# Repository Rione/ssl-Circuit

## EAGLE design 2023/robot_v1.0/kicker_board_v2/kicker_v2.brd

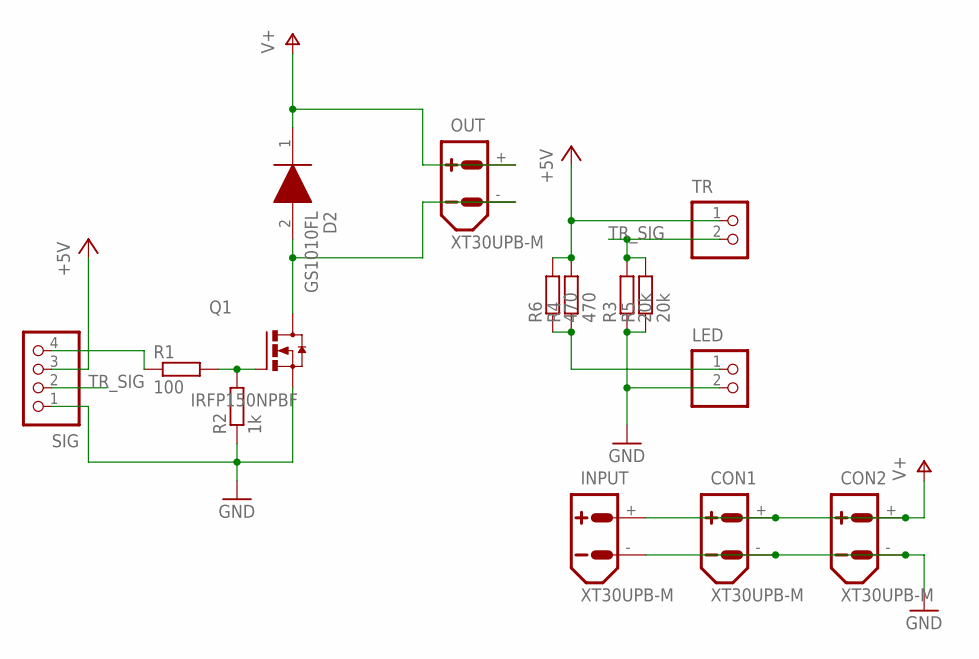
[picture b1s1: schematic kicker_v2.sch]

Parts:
CON1, CON2: XT30UPB-M
D2: GS1010FL; SODFL3618X110N
INPUT: XT30UPB-M
LED: S2B-XH-A
OUT: XT30UPB-M
Q1: IRFP150NPBF; TO-247AC
R1: 100; R0603
R2: 1k; R0603
R3: 20k; 0207/10
R4: 470; 0207/10
R5: 20k; R0603
R6: 470; R0603
SIG: B4B-XH-A
TR: S2B-XH-A

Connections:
1: D2.2 (A), OUT.-, Q1.D
+5V: R4.2, R6.2, SIG.3, TR.1
GND: CON1.-, CON2.-, INPUT.-, LED.2, Q1.S, R2.1, R3.1, R5.1, SIG.1
unnamed: R1.1, SIG.4
unnamed: Q1.G, R1.2, R2.2
unnamed: LED.1, R4.1, R6.1
TR_SIG: R3.2, R5.2, SIG.2, TR.2
V+: CON1.+, CON2.+, D2.1 (K), INPUT.+, OUT.+

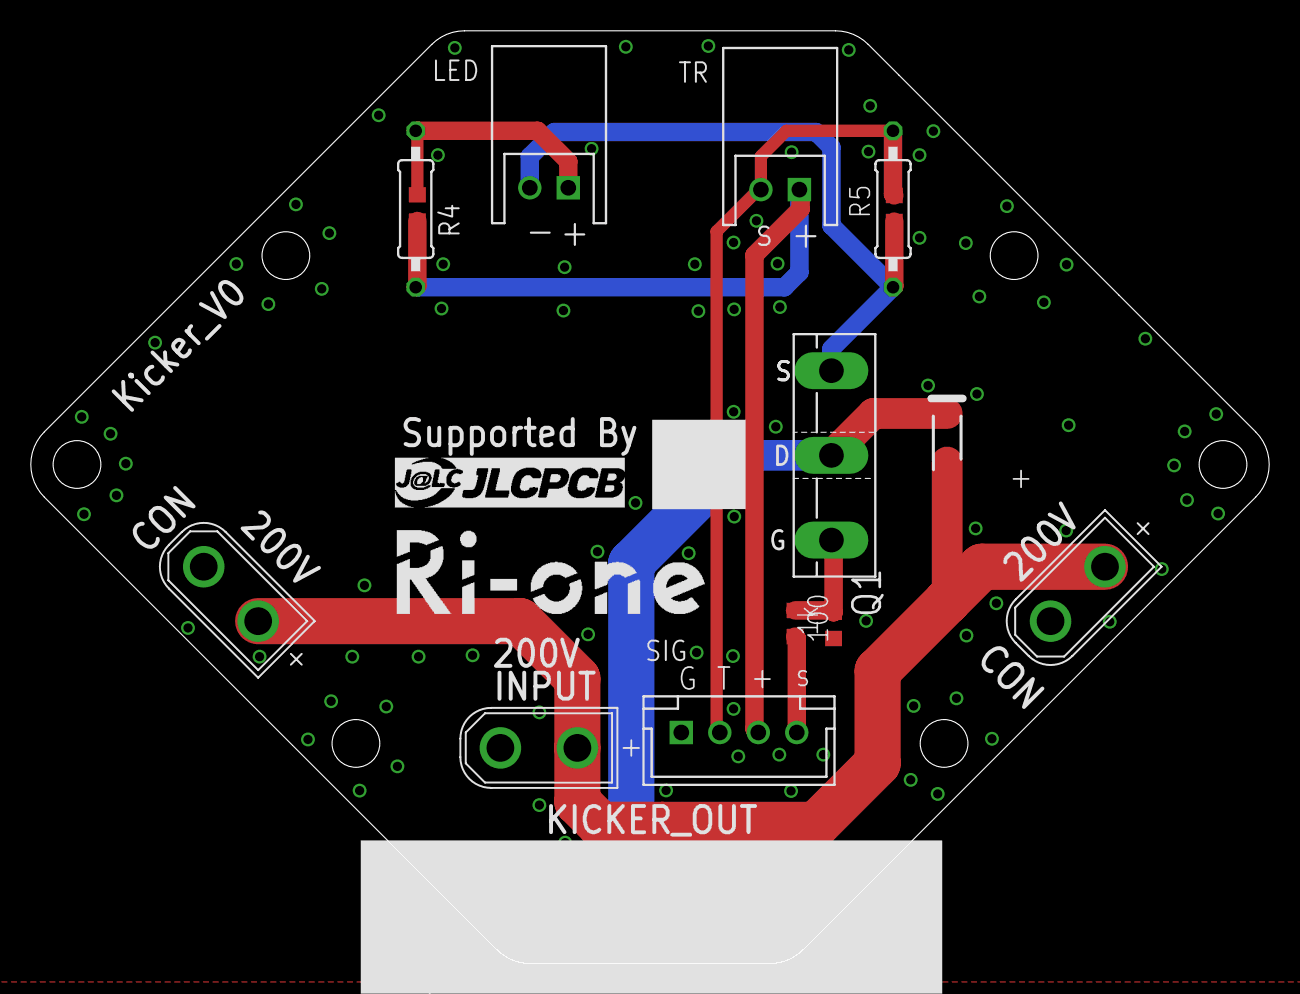
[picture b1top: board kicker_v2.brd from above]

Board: 2 copper layers, 80.4 x 60.6 mm, 15 parts (0 on the bottom side), 8 nets.

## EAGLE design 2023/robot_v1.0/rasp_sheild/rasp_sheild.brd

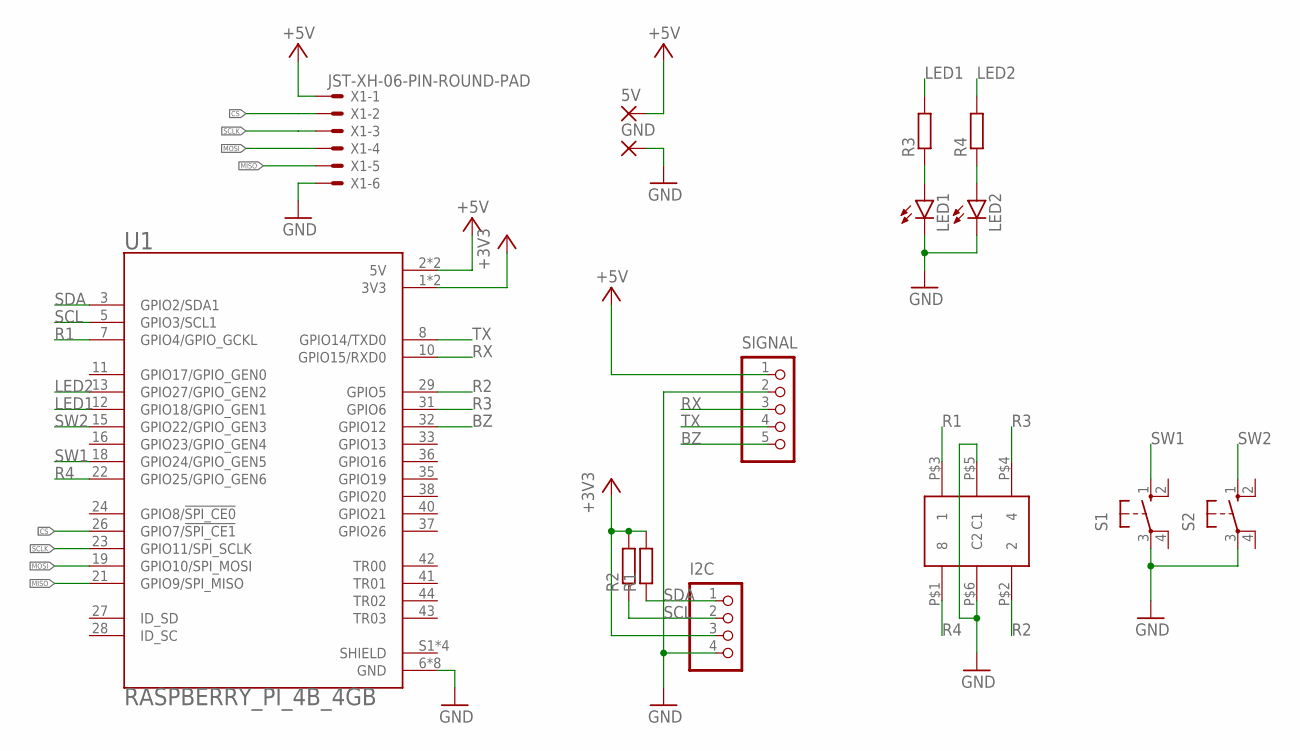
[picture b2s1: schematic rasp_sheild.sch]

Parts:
5V: SMD2; SMD1,27-2,54
DIP: DIP_RSW
GND: SMD2; SMD1,27-2,54
I2C: B4B-XH-A
LED1, LED2: LEDCHIPLED_0805; CHIPLED_0805
R1, R2, R3, R4: R-EU_R0805; R0805
S1, S2: 10-XX; B3F-10XX
SIGNAL: B5B-XH-A
U1: RASPBERRY_PI_4B_4GB; MODULE_RASPBERRY_PI_4B_4GB
X1: JST-XH-06-PIN-ROUND-PAD; JST-XH-06-PACKAGE-ROUND-PAD

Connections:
+3V3: I2C.3, R1.2, R2.2, U1.1 (3V3), U1.17 (3V3)
+5V: 5V.1, SIGNAL.1, U1.2 (5V), U1.4 (5V), X1.1
BZ: SIGNAL.5, U1.32 (GPIO12)
CS: U1.26 (GPIO7/!SPI_CE1!), X1.2
GND: DIP.P$5 (C1), DIP.P$6 (C2), GND.1, I2C.4, LED1.C, LED2.C, S1.3, S2.3, SIGNAL.2, U1.6 (GND), U1.9 (GND), U1.14 (GND), U1.20 (GND), U1.25 (GND), U1.30 (GND), U1.34 (GND), U1.39 (GND), X1.6
LED1: R3.2, U1.12 (GPIO18/GPIO_GEN1)
LED2: R4.2, U1.13 (GPIO27/GPIO_GEN2)
MISO: U1.21 (GPIO9/SPI_MISO), X1.5
MOSI: U1.19 (GPIO10/SPI_MOSI), X1.4
unnamed: LED2.A, R4.1
unnamed: LED1.A, R3.1
R1: DIP.P$3 (1), U1.7 (GPIO4/GPIO_GCKL)
R2: DIP.P$2 (2), U1.29 (GPIO5)
R3: DIP.P$4 (4), U1.31 (GPIO6)
R4: DIP.P$1 (8), U1.22 (GPIO25/GPIO_GEN6)
RX: SIGNAL.3, U1.10 (GPIO15/RXD0)
SCL: I2C.2, R2.1, U1.5 (GPIO3/SCL1)
SCLK: U1.23 (GPIO11/SPI_SCLK), X1.3
SDA: I2C.1, R1.1, U1.3 (GPIO2/SDA1)
SHIELD: U1.S1 (SHIELD), U1.S2 (SHIELD), U1.S3 (SHIELD), U1.S4 (SHIELD)
SW1: S1.1 (S), U1.18 (GPIO24/GPIO_GEN5)
SW2: S2.1 (S), U1.15 (GPIO22/GPIO_GEN3)
TX: SIGNAL.4, U1.8 (GPIO14/TXD0)

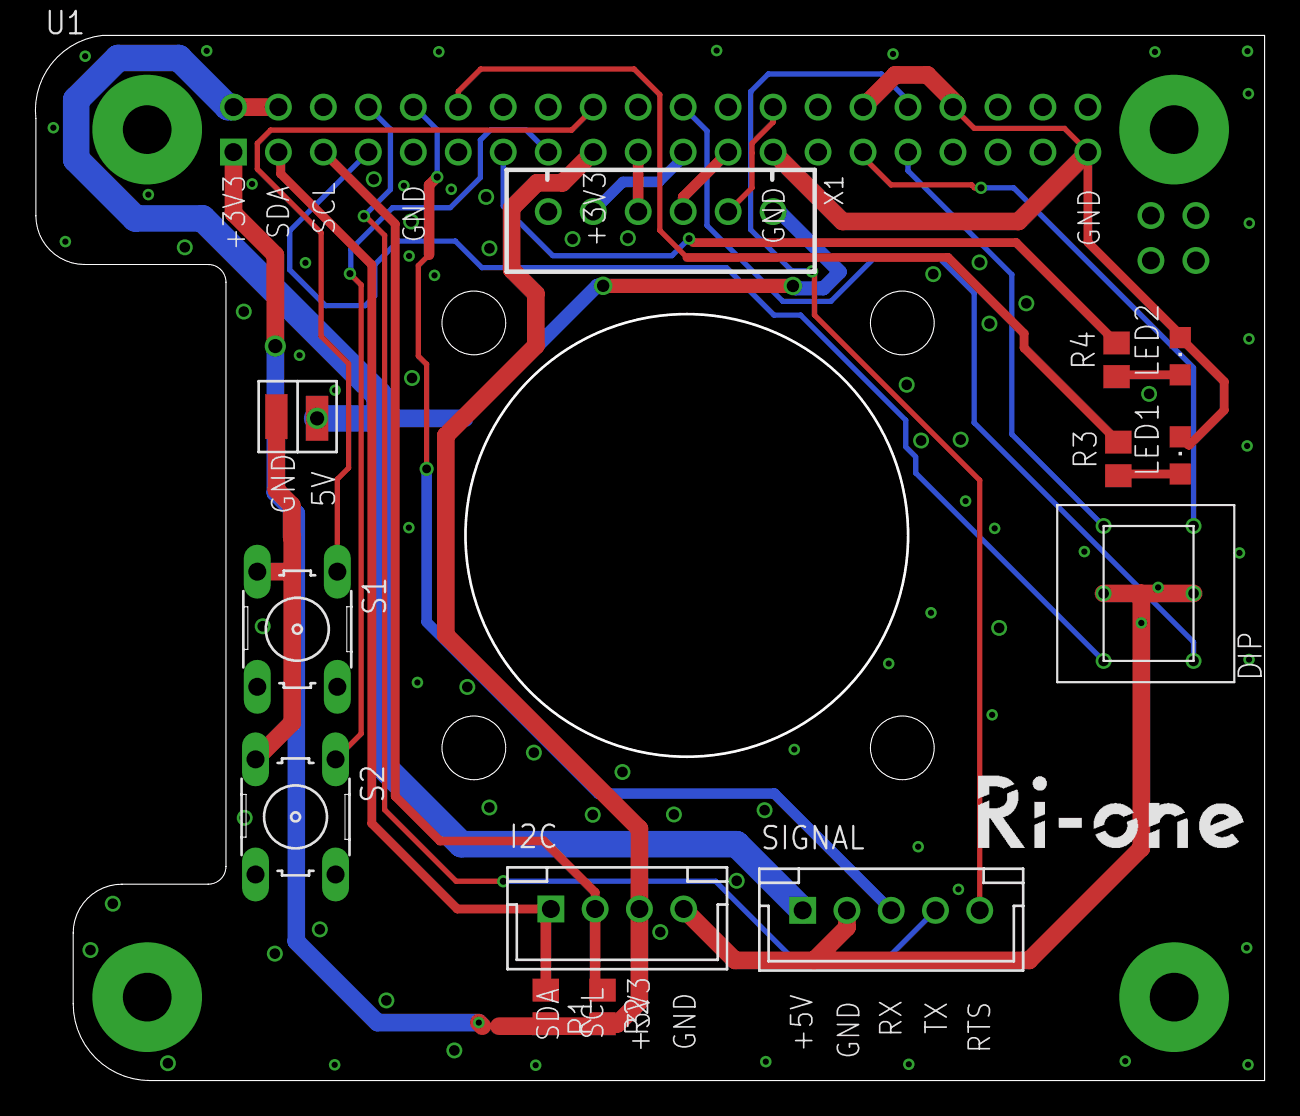
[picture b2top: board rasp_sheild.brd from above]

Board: 2 copper layers, 69.4 x 59.0 mm, 15 parts (0 on the bottom side), 23 nets.

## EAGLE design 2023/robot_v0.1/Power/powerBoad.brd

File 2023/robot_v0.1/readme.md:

# Main and Power 

- 小さくしたかったので試作しました

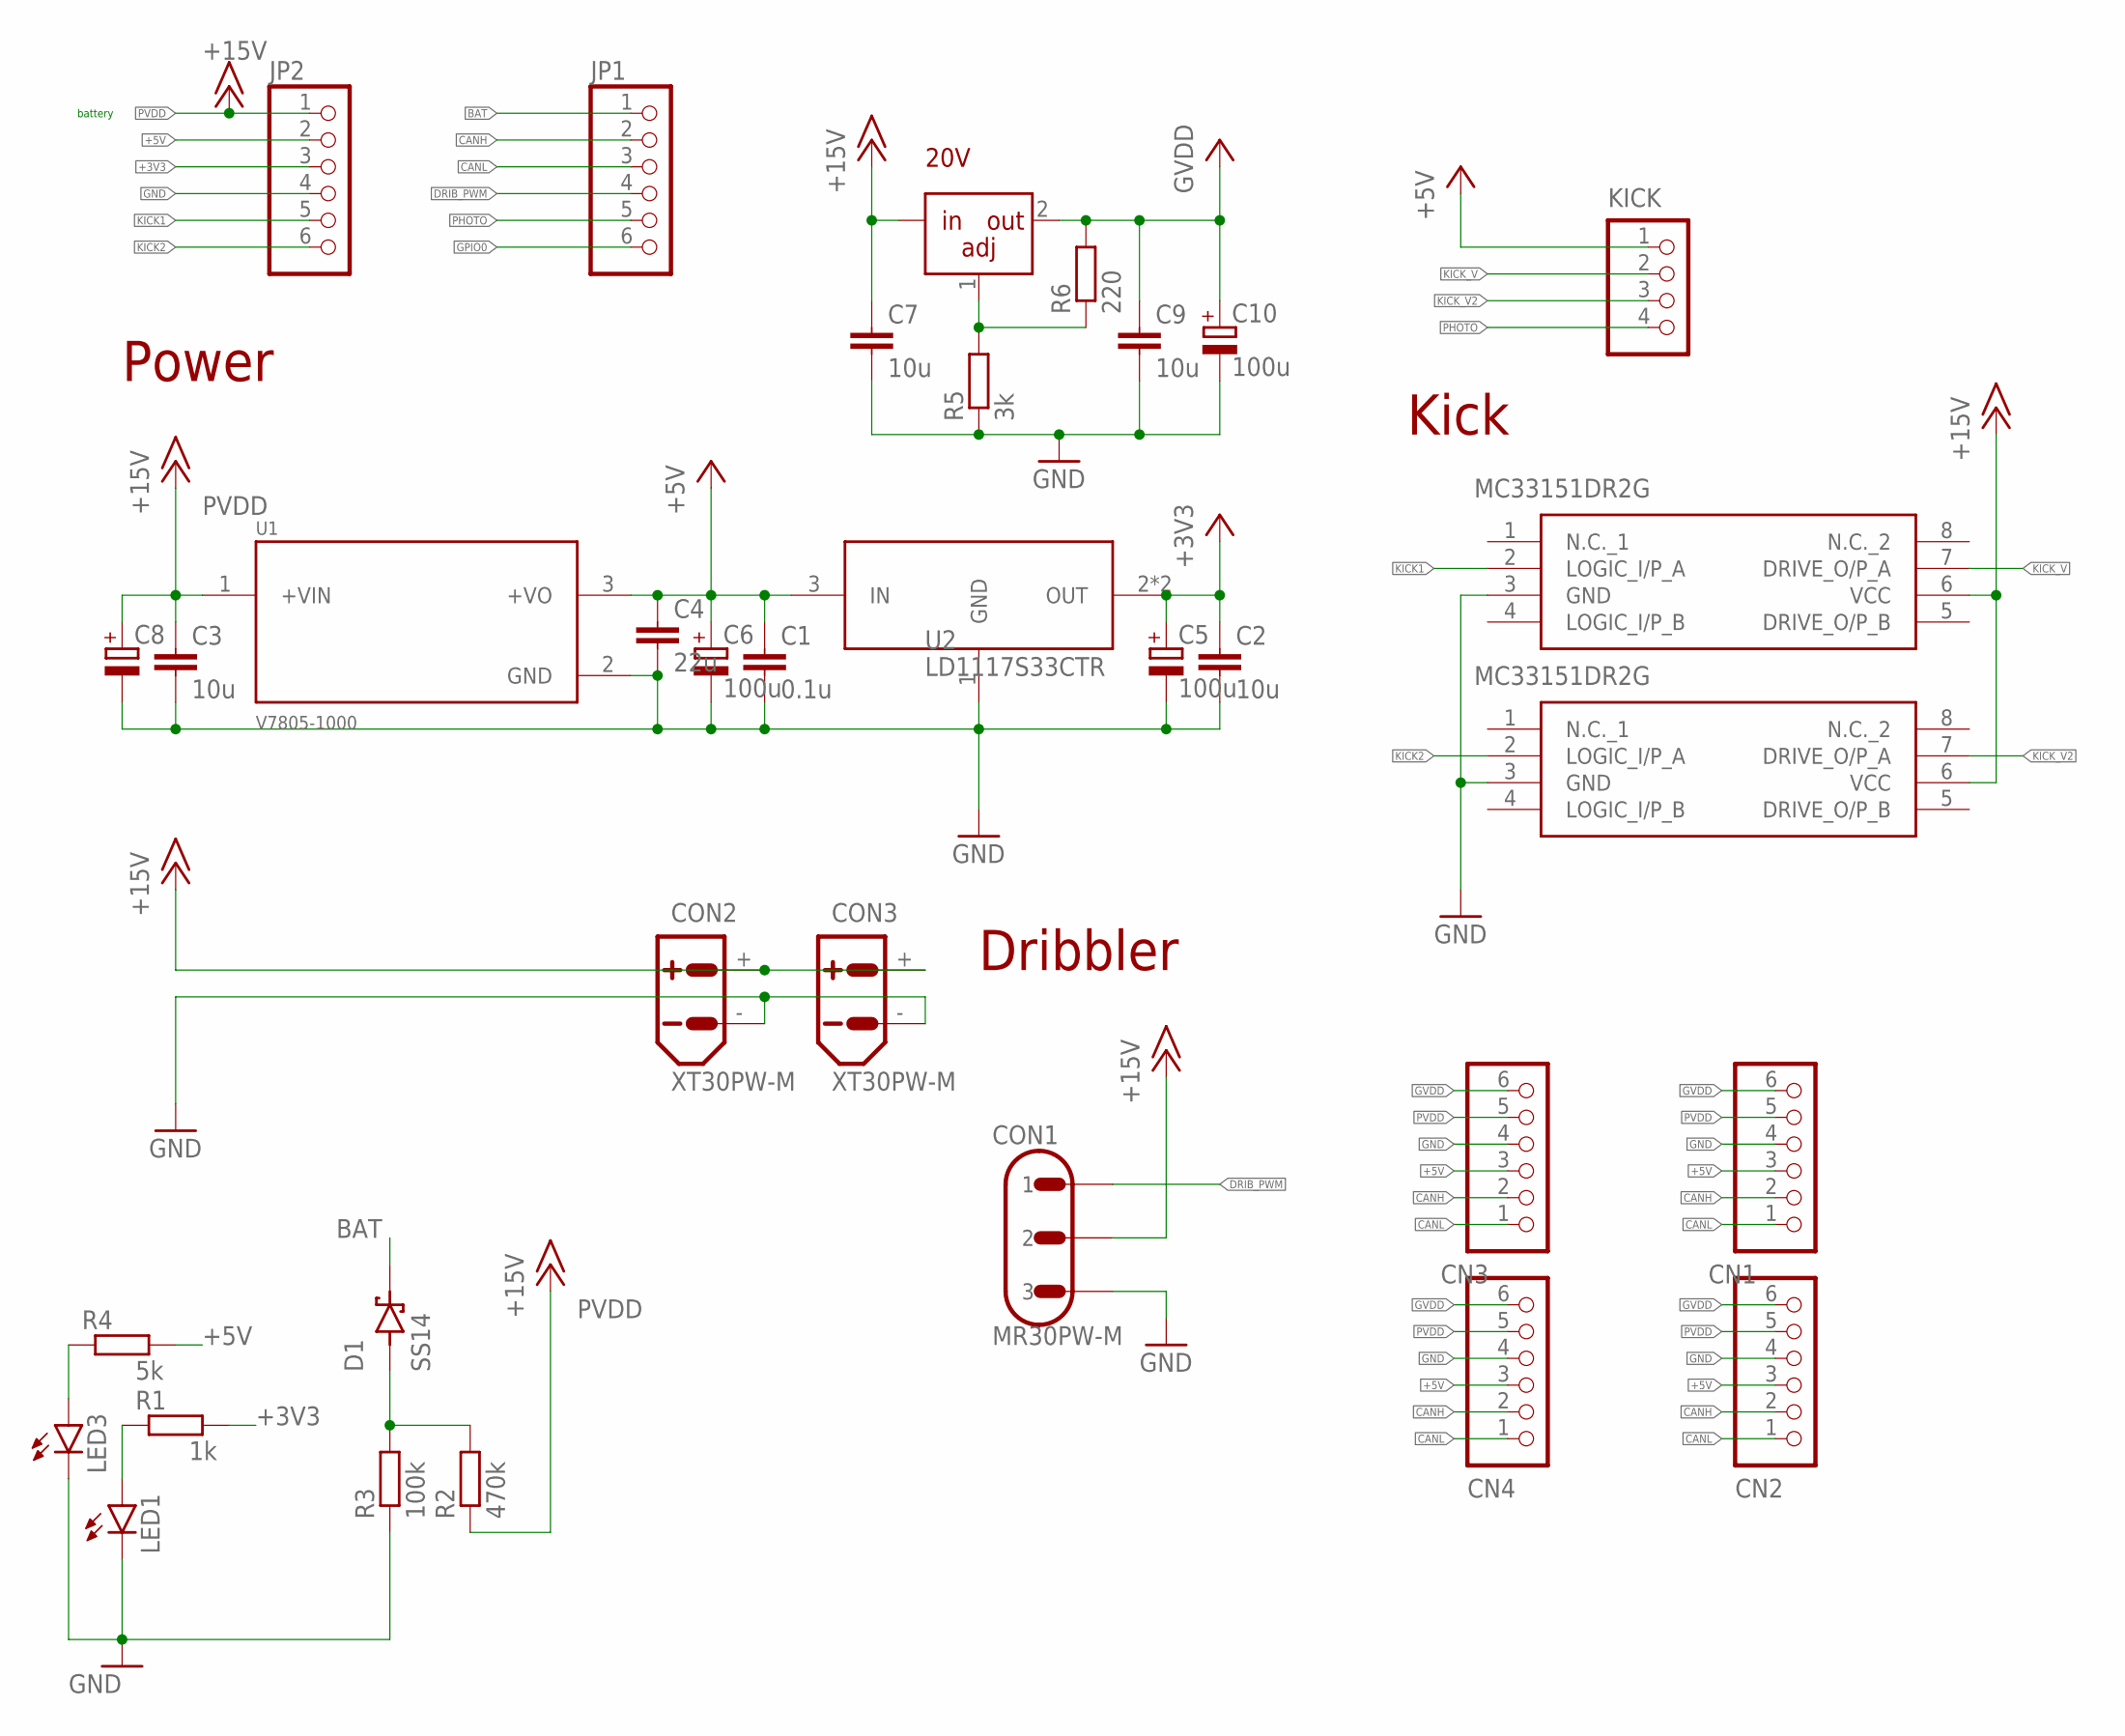
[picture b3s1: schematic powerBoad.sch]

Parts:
C1: 0.1u; C1608
C2, C3, C7, C9: 10u; C1608
C4: 22u; C2012
C5, C6, C10: 100u; 153CLV-0605
C8: CPOL-EU140CLH-1010; 140CLH-1010
CN1, CN2, CN3, CN4: S6B-XH-A
CON1: MR30PW-M
CON2, CON3: XT30PW-M
D1: SS14; DIOM4325X250N
JP1, JP2: PINHD-1X6; 1X06
KICK: S4B-XH-A
LED1, LED3: LEDCHIPLED_0603; CHIPLED_0603
R1: 1k; R0603
R2: 470k; R0603
R3: 100k; R0603
R4: 5k; R0603
R5: 3k; R0603
R6: 220; R0603
U1: V7805-1000; CONV_V7805-1000
U2: LD1117S33CTR; SOT223
U3, U4: MC33151DR2G; SOIC127P600X175-8N
U$1: NJM317DL1; DPAK228P968X238-4N

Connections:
2: D1.A, R2.2, R3.2
+3V3: C2.1, C5.+, JP2.3, R1.2, U2.2 (OUT), U2.4 (OUT)
+5V: C1.1, C4.1, C6.+, CN1.3, CN2.3, CN3.3, CN4.3, JP2.2, KICK.1, R4.2, U1.3 (+VO), U2.3 (IN)
+15V: C7.1, U$1.3 (IN)
BAT: D1.C (K), JP1.1
CANH: CN1.2, CN2.2, CN3.2, CN4.2, JP1.2
CANL: CN1.1, CN2.1, CN3.1, CN4.1, JP1.3
DRIB_PWM: CON1.1, JP1.4
GND: C1.2, C2.2, C3.2, C4.2, C5.-, C6.-, C7.2, C8.-, C9.2, C10.-, CN1.4, CN2.4, CN3.4, CN4.4, CON1.3, CON2.-, CON3.-, JP2.4, LED1.C, LED3.C, R3.1, R5.1, U1.2 (GND), U2.1 (GND), U3.3 (GND), U4.3 (GND)
GPIO0: JP1.6
GVDD: C9.1, C10.+, CN1.6, CN2.6, CN3.6, CN4.6, R6.2, U$1.2 (OUT)
KICK1: JP2.5, U3.2 (LOGIC_I/P_A)
KICK2: JP2.6, U4.2 (LOGIC_I/P_A)
KICK_V: KICK.2, U3.7 (DRIVE_O/P_A)
KICK_V2: KICK.3, U4.7 (DRIVE_O/P_A)
unnamed: LED3.A, R4.1
unnamed: LED1.A, R1.1
unnamed: R5.2, R6.1, U$1.1 (ADJ)
PHOTO: JP1.5, KICK.4
PVDD: C3.1, C8.+, CN1.5, CN2.5, CN3.5, CN4.5, CON1.2, CON2.+, CON3.+, JP2.1, R2.1, U1.1 (+VIN), U3.6 (VCC), U4.6 (VCC)

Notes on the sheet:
Power
Dribbler
Kick
battery
20V

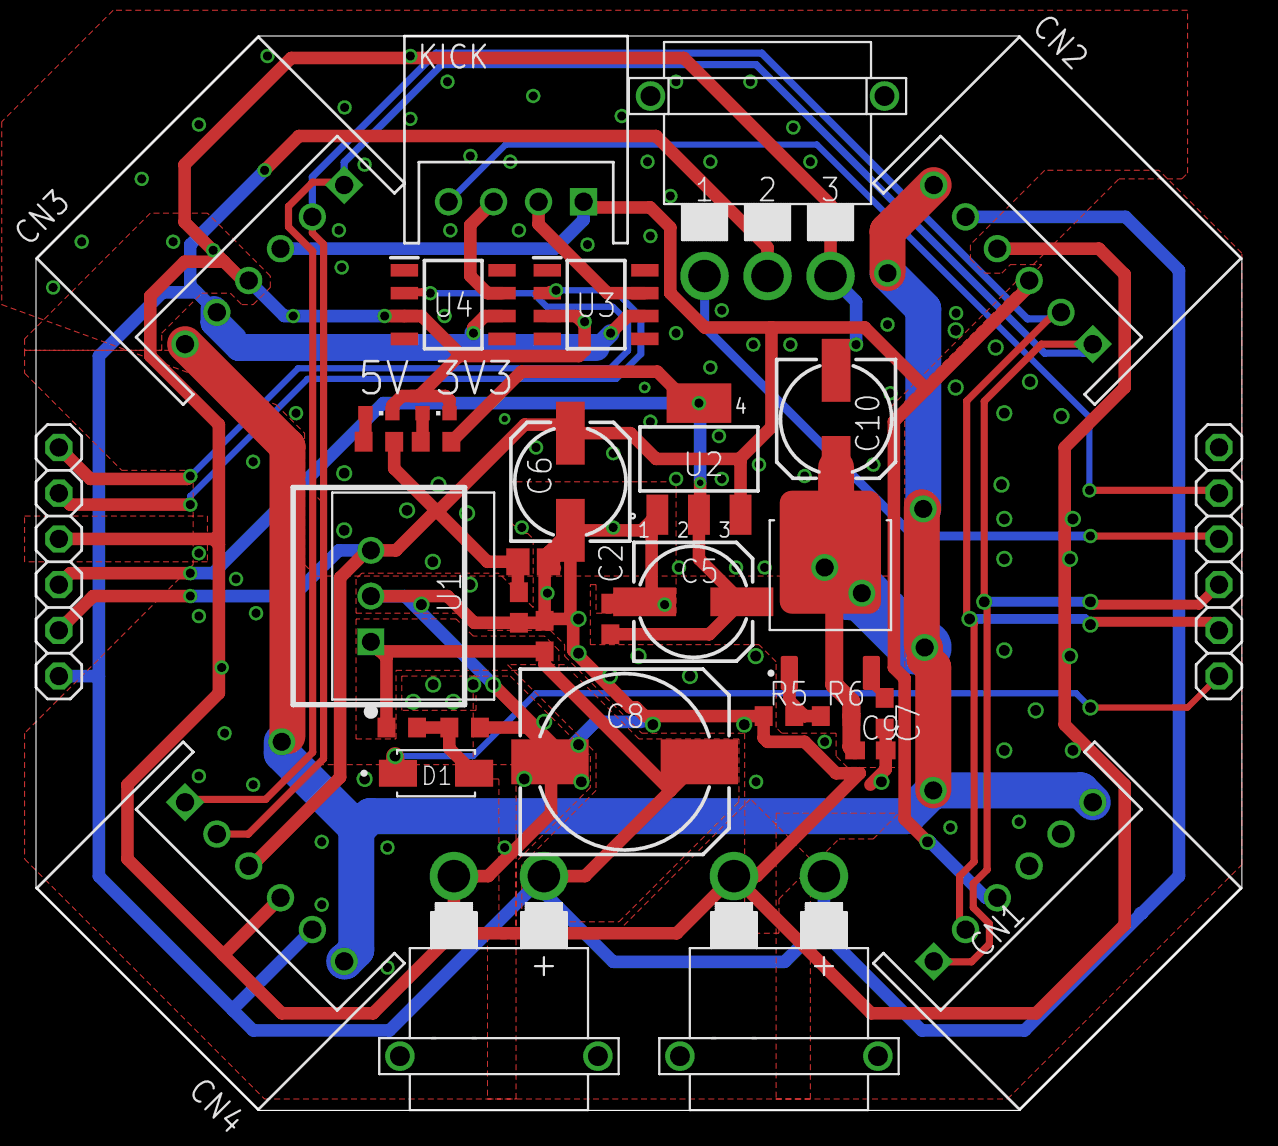
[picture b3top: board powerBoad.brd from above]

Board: 2 copper layers, 67.0 x 59.7 mm, 34 parts (0 on the bottom side), 19 nets.

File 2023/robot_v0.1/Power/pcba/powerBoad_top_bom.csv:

Comment,Designator,Footprint,LCSC Part #
0.1u,C1,C1608,
1k,R1,R0603,
3k,R5,R0603,
5k,R4,R0603,
10u,C2 C3 C7 C9,C1608,
22u,C4,C2012,
100k,R3,R0603,
100u,C5 C6 C10,153CLV-0605,
220,R6,R0603,
470k,R2,R0603,
LD1117S33CTR,U2,SOT223,
MC33151DR2G,U3 U4,SOIC127P600X175-8N,
NJM317DL1,U$1,DPAK228P968X238-4N,
SS14,D1,DIOM4325X250N,

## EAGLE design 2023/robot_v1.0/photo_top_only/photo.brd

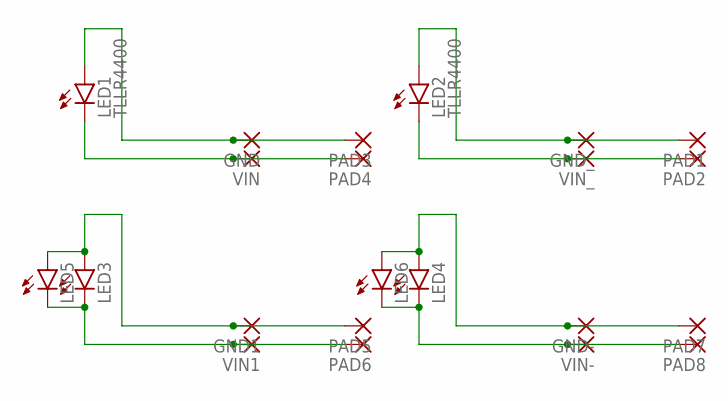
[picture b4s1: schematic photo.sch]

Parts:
GND, GND1: SMD2; SMD1,27-2,54
GND-: SMD2; SMD1,27-2,54
GND_: SMD2; SMD1,27-2,54
LED1, LED2: TLLR4400; LED3MM
LED3, LED4, LED5, LED6: LEDCHIP-LED0805; CHIP-LED0805
PAD1, PAD2, PAD3, PAD4, PAD5, PAD6, PAD7, PAD8: SMD2; SMD1,27-2,54
VIN, VIN1: SMD2; SMD1,27-2,54
VIN-: SMD2; SMD1,27-2,54
VIN_: SMD2; SMD1,27-2,54

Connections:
unnamed: LED1.K (C), PAD4.1, VIN.1
unnamed: GND.1, LED1.A, PAD3.1
unnamed: GND_.1, LED2.A, PAD1.1
unnamed: LED2.K (C), PAD2.1, VIN_.1
unnamed: GND1.1, LED3.A, LED5.A, PAD5.1
unnamed: LED3.C, LED5.C, PAD6.1, VIN1.1
unnamed: GND-.1, LED4.A, LED6.A, PAD7.1
unnamed: LED4.C, LED6.C, PAD8.1, VIN-.1

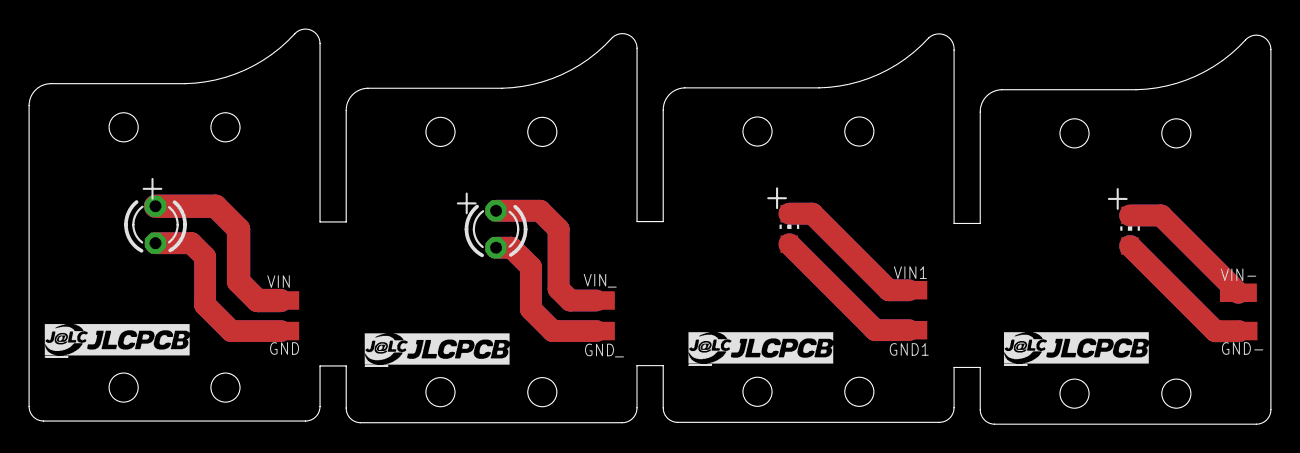
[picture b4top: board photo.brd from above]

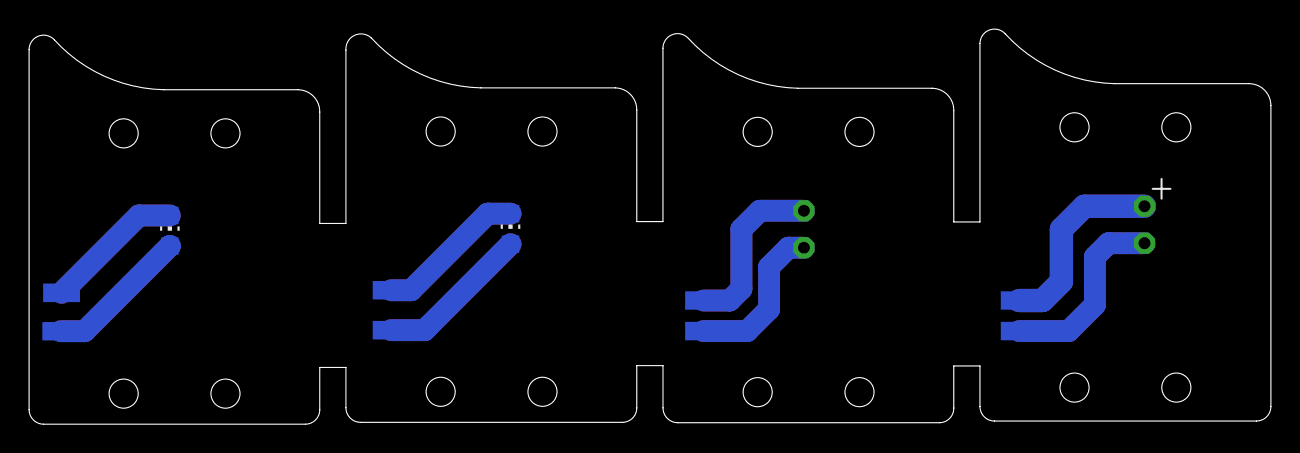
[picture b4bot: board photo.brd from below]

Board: 2 copper layers, 85.4 x 27.2 mm, 22 parts (10 on the bottom side), 8 nets.

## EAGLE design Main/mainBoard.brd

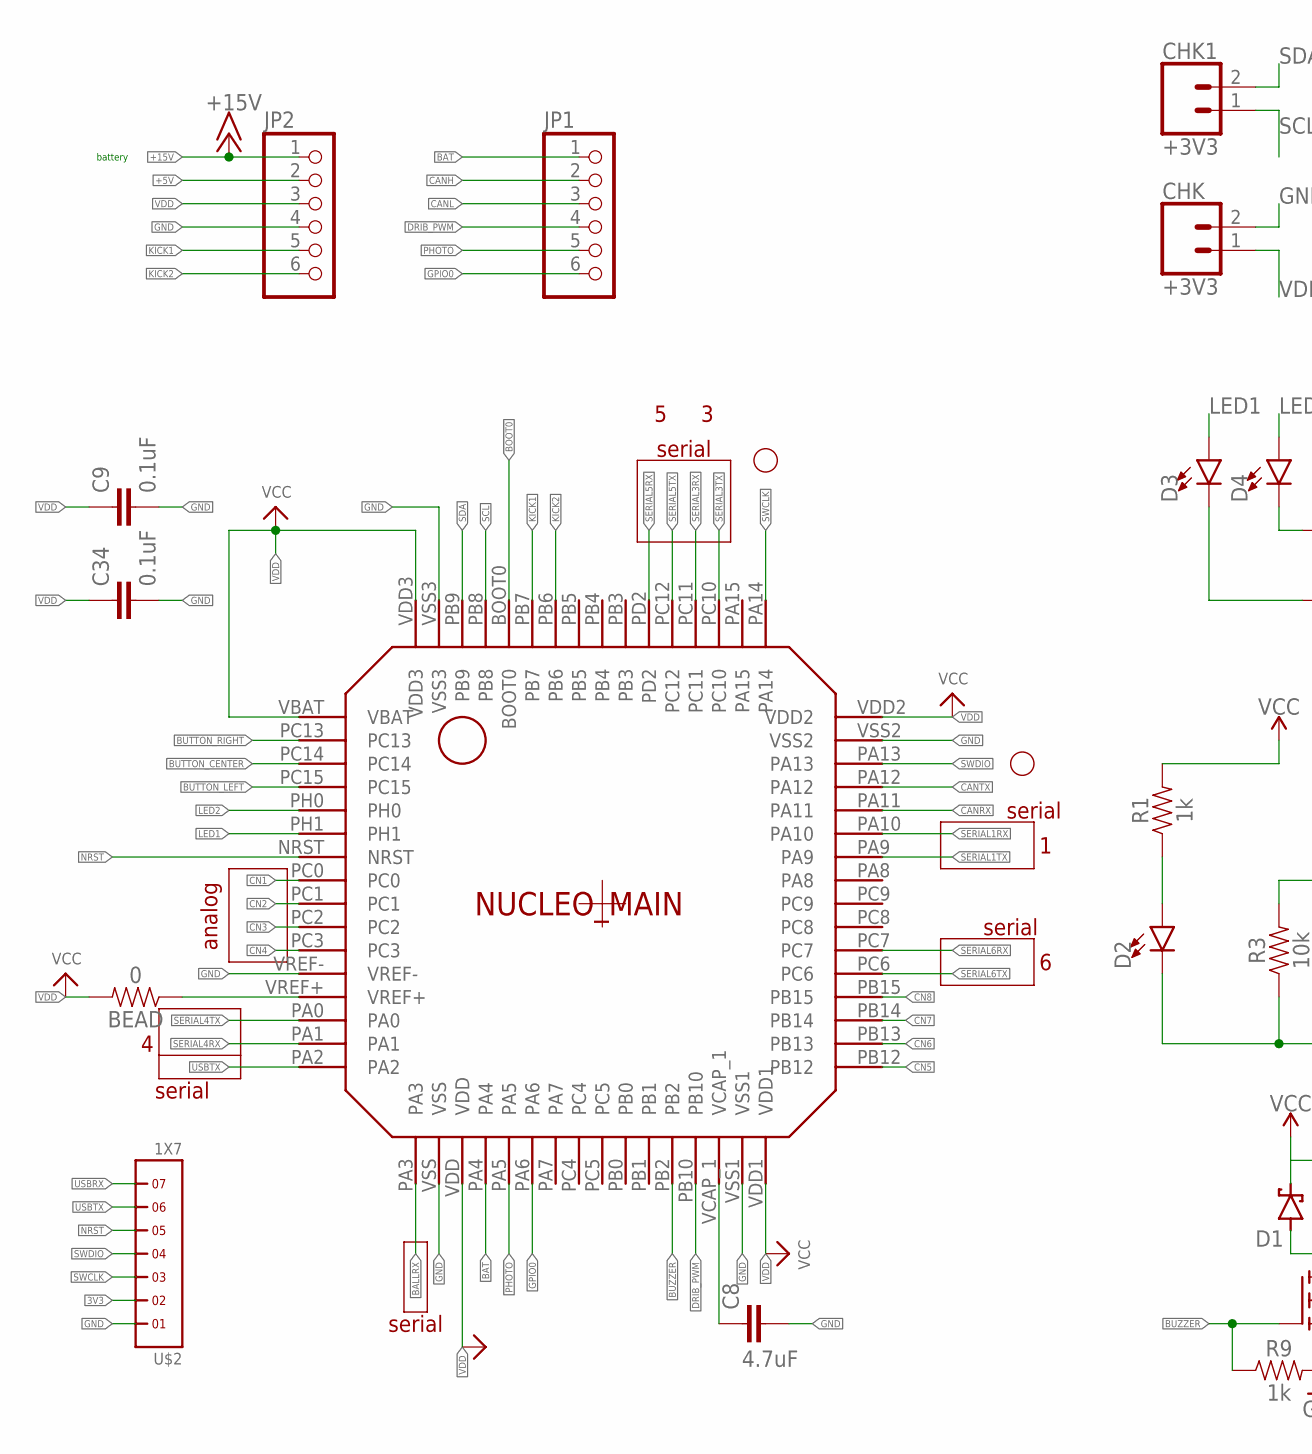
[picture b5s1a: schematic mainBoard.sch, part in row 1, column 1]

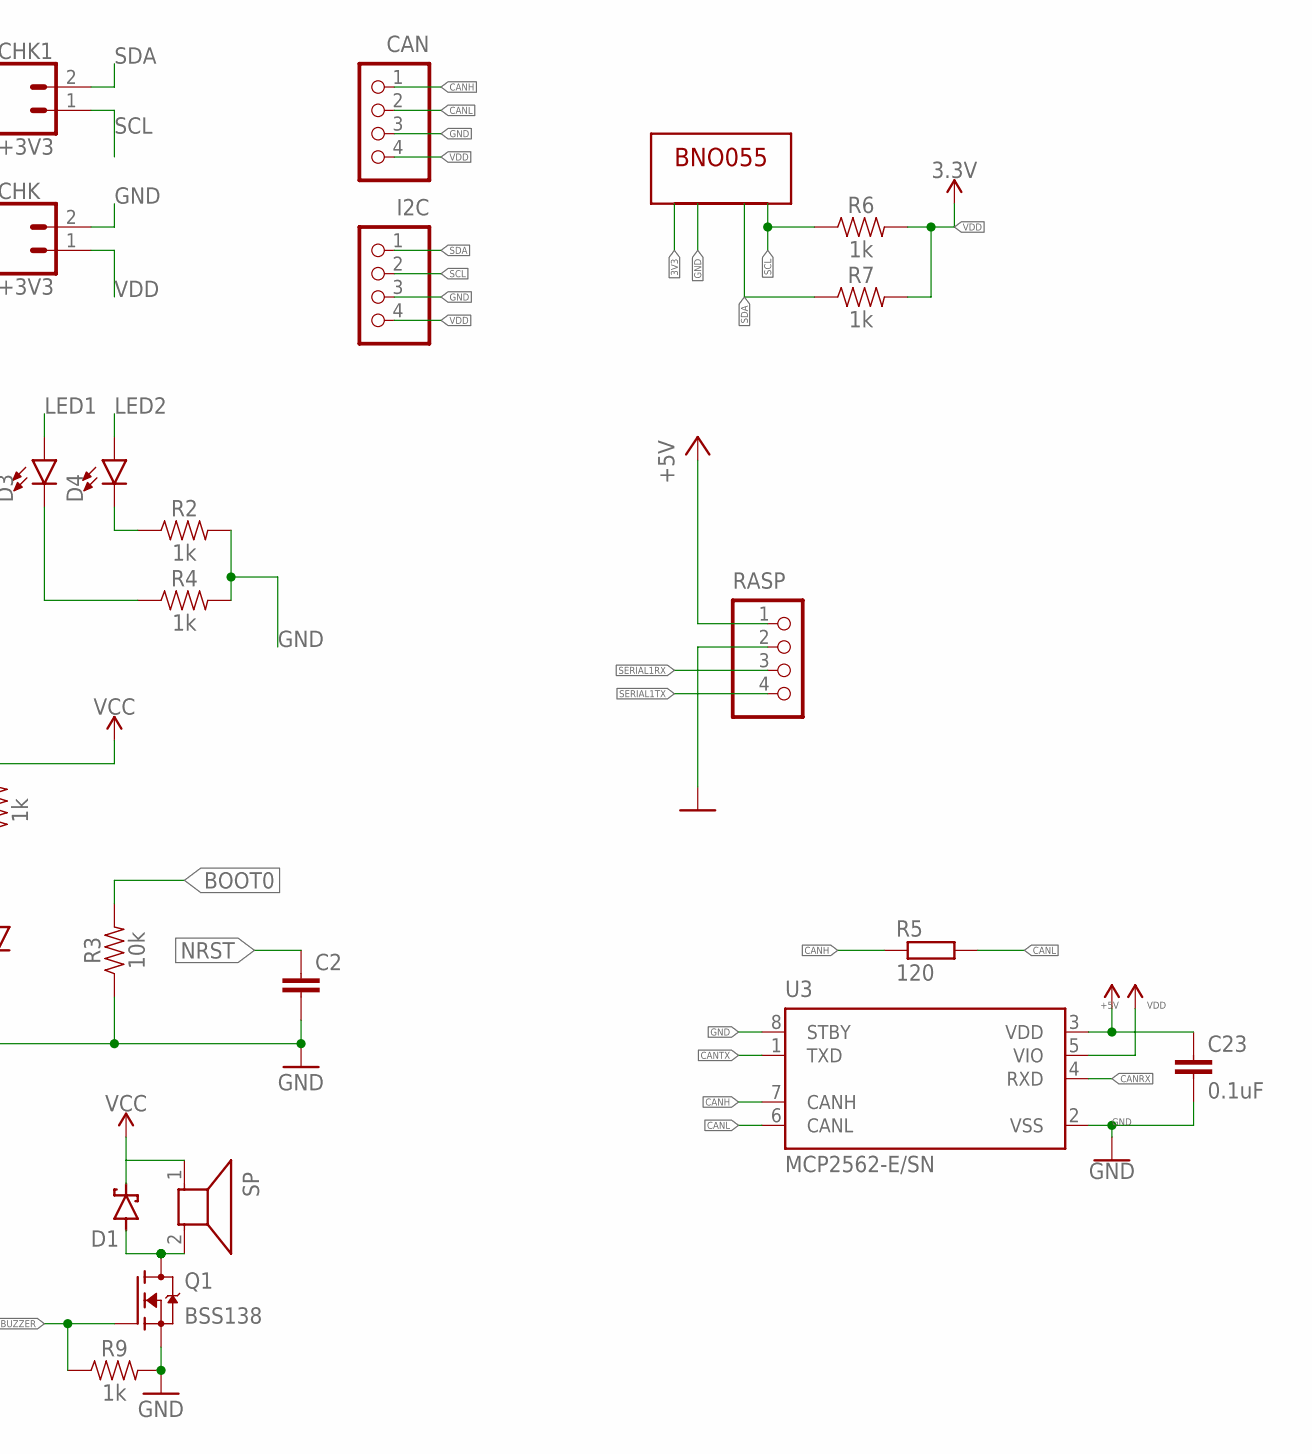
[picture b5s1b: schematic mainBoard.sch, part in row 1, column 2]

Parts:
BEAD: 0; 0603
C2: 0.1UF_1608; 1608
C8: 4.7uF; 0603
C9, C23, C34: 0.1uF; 0603
CAN: S4B-XH-A
CHK, CHK1: +3V3; 1X02
D1: DIODE-SS2040LFL; SOD123FL
D2, D3, D4: LED0603; LED-0603
I2C: S4B-XH-A
JP1, JP2: PINHD-1X6; 1X06
NUCLEO_MAIN: F446RET6; STM32F446RET6
Q1: BSS138; SOT95P240X111-3N
R1, R2, R4, R9: 1k; R0603
R3: 10k; R0603
R5: 120; R0603
R6, R7: 1k; 0603
RASP: B4B-XH-A
SP: PKLCS1212E4001
U3: MCP2562-E/SN; SOIC127P600X175-8N
U$2: 1X7
U$3: AE-BNO055-BO

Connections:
3V3: U$2.2, U$3.VIN
+5V: C23.1, JP2.2, RASP.1, U3.3 (VDD)
+15V: JP2.1
BALLRX: NUCLEO_MAIN.PA3
BAT: JP1.1, NUCLEO_MAIN.PA4
BOOT0: NUCLEO_MAIN.BOOT0, R3.2
BUTTON_CENTER: NUCLEO_MAIN.PC14
BUTTON_LEFT: NUCLEO_MAIN.PC15
BUTTON_RIGHT: NUCLEO_MAIN.PC13
BUZZER: NUCLEO_MAIN.PB2, Q1.1 (G), R9.1
CANH: CAN.1, JP1.2, R5.1, U3.7 (CANH)
CANL: CAN.2, JP1.3, R5.2, U3.6 (CANL)
CANRX: NUCLEO_MAIN.PA11, U3.4 (RXD)
CANTX: NUCLEO_MAIN.PA12, U3.1 (TXD)
CN1: NUCLEO_MAIN.PC0
CN2: NUCLEO_MAIN.PC1
CN3: NUCLEO_MAIN.PC2
CN4: NUCLEO_MAIN.PC3
CN5: NUCLEO_MAIN.PB12
CN6: NUCLEO_MAIN.PB13
CN7: NUCLEO_MAIN.PB14
CN8: NUCLEO_MAIN.PB15
DRIB_PWM: JP1.4, NUCLEO_MAIN.PB10
GND: C2.2, C8.2, C9.2, C23.2, C34.2, CAN.3, CHK.2, D2.C, I2C.3, JP2.4, NUCLEO_MAIN.VREF-, NUCLEO_MAIN.VSS, NUCLEO_MAIN.VSS1, NUCLEO_MAIN.VSS2, NUCLEO_MAIN.VSS3, Q1.2 (S), R2.2, R3.1, R4.2, R9.2, RASP.2, U3.2 (VSS), U3.8 (STBY), U$2.1, U$3.GND
GPIO0: JP1.6, NUCLEO_MAIN.PA6
KICK1: JP2.5, NUCLEO_MAIN.PB7
KICK2: JP2.6, NUCLEO_MAIN.PB6
LED1: D3.A, NUCLEO_MAIN.PH1
LED2: D4.A, NUCLEO_MAIN.PH0
unnamed: D4.C, R2.1
unnamed: D3.C, R4.1
unnamed: D1.C, SP.1
unnamed: D1.A, Q1.3 (D), SP.2
NRST: C2.1, NUCLEO_MAIN.NRST, U$2.5
PHOTO: JP1.5, NUCLEO_MAIN.PA5
POWERLED_RESISTOR: D2.A, R1.1
SCL: CHK1.1, I2C.2, NUCLEO_MAIN.PB8, R6.1, U$3.SCL
SDA: CHK1.2, I2C.1, NUCLEO_MAIN.PB9, R7.1, U$3.SDA
SERIAL1RX: NUCLEO_MAIN.PA10, RASP.3
SERIAL1TX: NUCLEO_MAIN.PA9, RASP.4
SERIAL3RX: NUCLEO_MAIN.PC11
SERIAL3TX: NUCLEO_MAIN.PC10
SERIAL4RX: NUCLEO_MAIN.PA1
SERIAL4TX: NUCLEO_MAIN.PA0
SERIAL5RX: NUCLEO_MAIN.PD2
SERIAL5TX: NUCLEO_MAIN.PC12
SERIAL6RX: NUCLEO_MAIN.PC7
SERIAL6TX: NUCLEO_MAIN.PC6
SWCLK: NUCLEO_MAIN.PA14, U$2.3
SWDIO: NUCLEO_MAIN.PA13, U$2.4
USBRX: U$2.7
USBTX: NUCLEO_MAIN.PA2, U$2.6
VCAP: C8.1, NUCLEO_MAIN.VCAP_1
VDD: BEAD.2, C9.1, C34.1, CAN.4, CHK.1, I2C.4, JP2.3, NUCLEO_MAIN.VBAT, NUCLEO_MAIN.VDD, NUCLEO_MAIN.VDD1, NUCLEO_MAIN.VDD2, NUCLEO_MAIN.VDD3, R1.2, R6.2, R7.2, U3.5 (VIO)
VDDA: BEAD.1, NUCLEO_MAIN.VREF+

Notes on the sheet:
serial
analog
battery

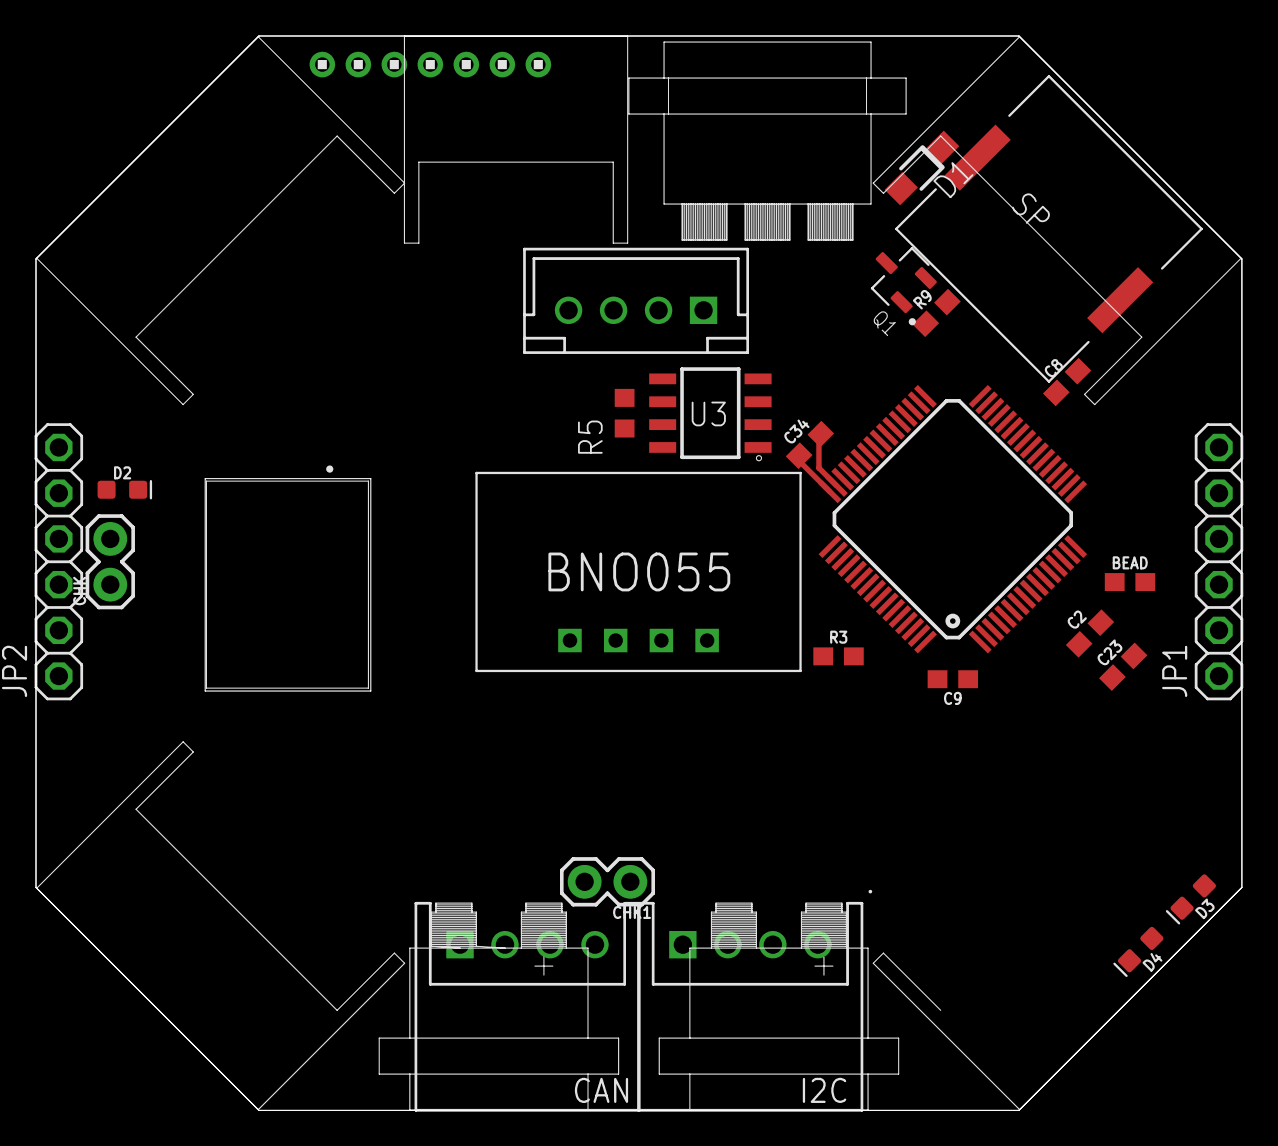
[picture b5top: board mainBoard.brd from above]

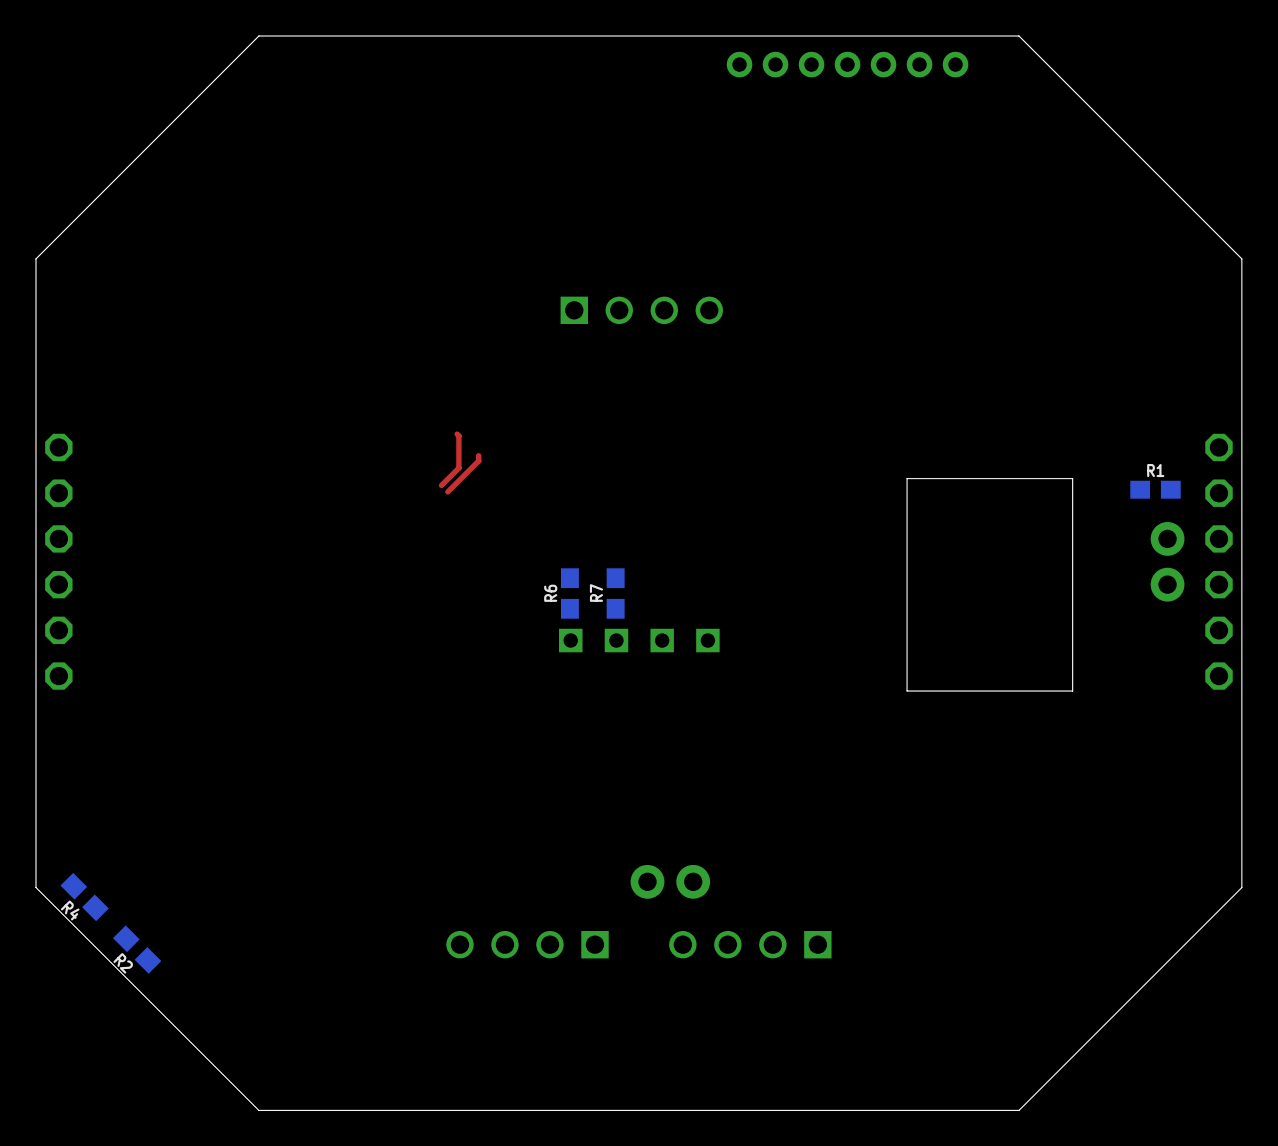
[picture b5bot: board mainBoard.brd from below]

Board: 2 copper layers, 67.0 x 59.7 mm, 31 parts (5 on the bottom side), 33 nets.

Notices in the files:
parts and their libraries:
SparkFun-Jumpers: Licensing: Creative Commons ShareAlike 4.0 International - https://creativecommons.org/licenses/by-sa/4.0
